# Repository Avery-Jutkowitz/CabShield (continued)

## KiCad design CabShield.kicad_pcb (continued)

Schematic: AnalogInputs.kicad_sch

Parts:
C12, C13, C14, C15: 1uf; C_0603_1608Metric; Manufacturer_Part_Number 0603B105K500XD
D7, D8, D9, D10, D11, D12, D13, D14: 1N4148W-7-F; Nexperia_CFP3_SOD-123W; Manufacturer_Part_Number 1N4148W-7-F
R23, R24, R25, R26, R27, R28, R29, R30: 1k; R_0402_1005Metric_Pad0.72x0.64mm_HandSolder; Manufacturer_Part_Number ERJ-2GEJ102X

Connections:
+3V3: D7.1 (K), D9.1 (K), D11.1 (K), D13.1 (K); also elsewhere on the board
/AI_1: C15.1, D13.2 (A), D14.1 (K), R29.1, R30.2; also elsewhere on the board
/AI_2: C14.1, D11.2 (A), D12.1 (K), R27.1, R28.2; also elsewhere on the board
/AI_3: C13.1, D9.2 (A), D10.1 (K), R25.1, R26.2; also elsewhere on the board
/AI_4: C12.1, D7.2 (A), D8.1 (K), R23.1, R24.2; also elsewhere on the board
/Analog Inputs/AI_conn1: R29.2; also elsewhere on the board
/Analog Inputs/AI_conn2: R27.2; also elsewhere on the board
/Analog Inputs/AI_conn3: R25.2; also elsewhere on the board
/Analog Inputs/AI_conn4: R23.2; also elsewhere on the board
GND: C12.2, C13.2, C14.2, C15.2, D8.2 (A), D10.2 (A), D12.2 (A), D14.2 (A), R24.1, R26.1, R28.1, R30.1; also elsewhere on the board

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
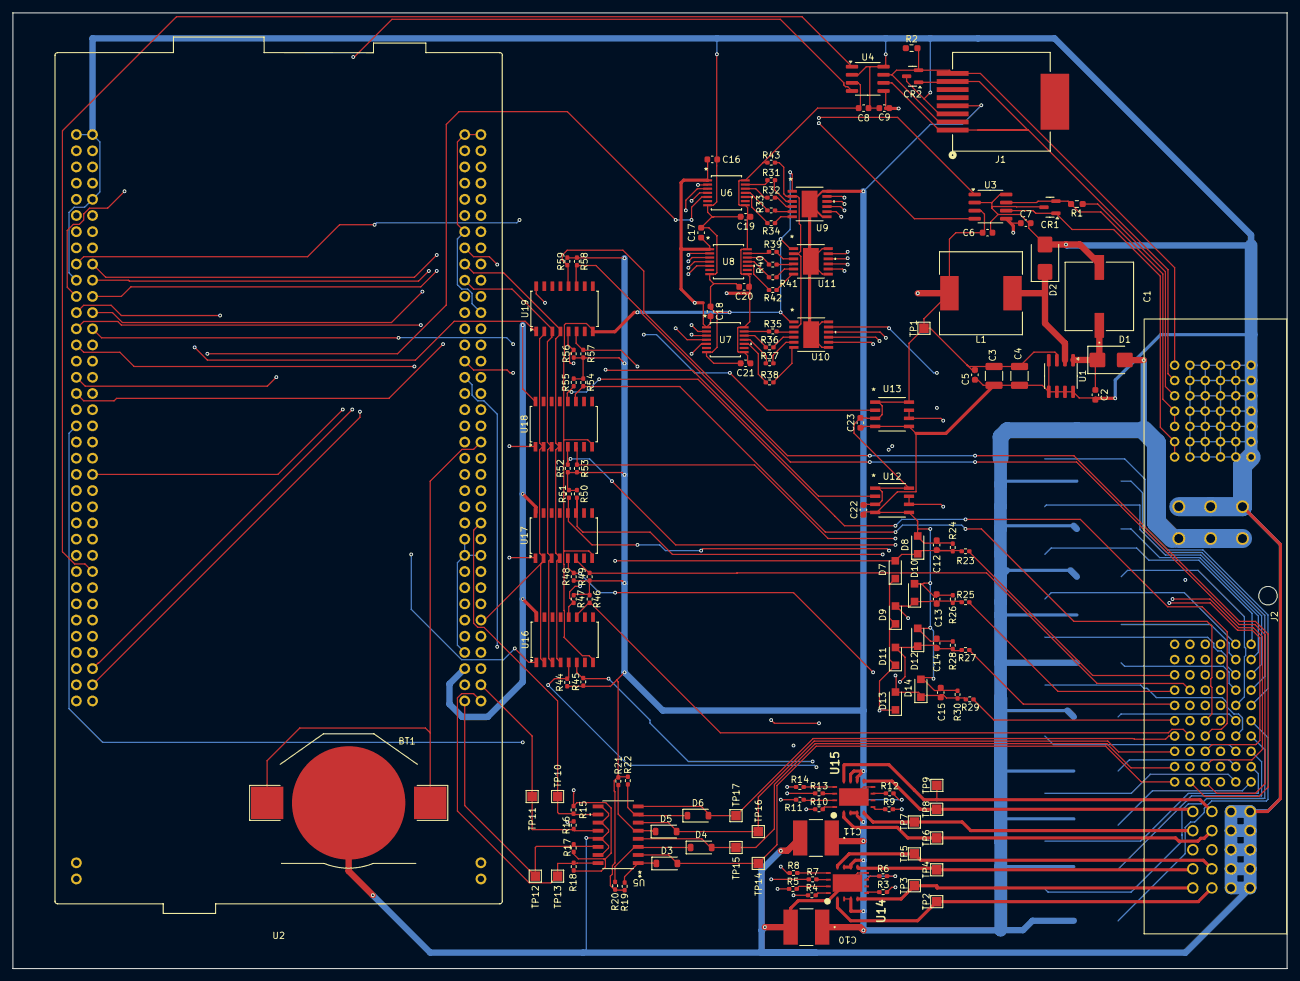
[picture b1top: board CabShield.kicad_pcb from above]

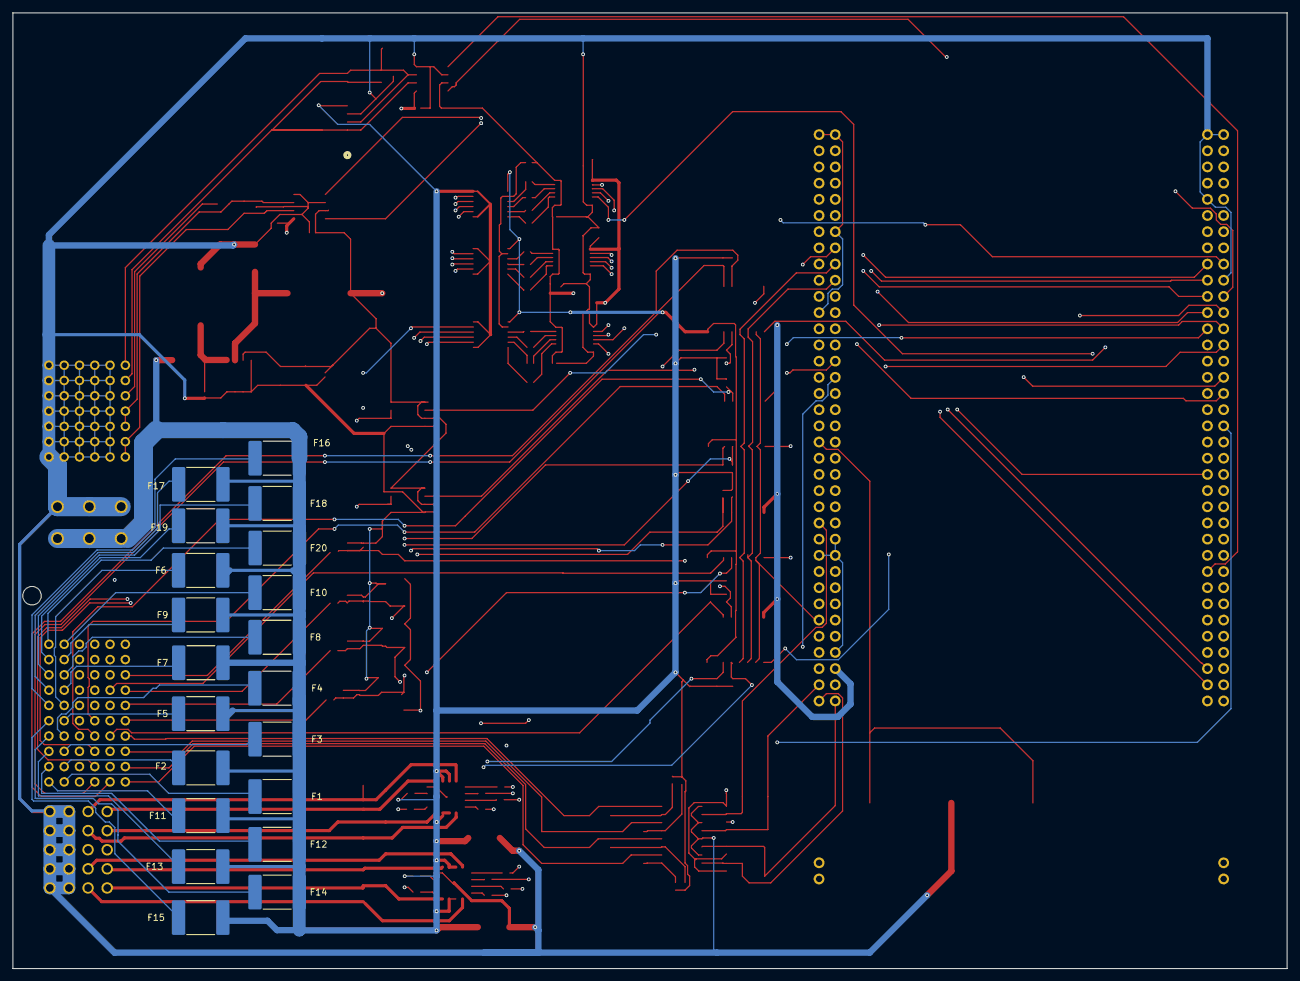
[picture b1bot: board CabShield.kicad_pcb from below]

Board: 4 copper layers, 200.0 x 150.0 mm, 158 parts (20 on the bottom side), 160 nets.

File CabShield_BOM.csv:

"Reference","Value","Description","Manufacturer_Part_Number","Datasheet","Footprint","Qty","DNP"
"BT1","3002","Single-cell battery","3002","https://www.keyelco.com/userAssets/file/M65p9.pdf","Battery:BatteryHolder_Keystone_3002_1x2032","1",""
"C1","EEE-FK1V471SP","Cap 470uF","EEE-FK1V471SP","https://api.pim.na.industrial.panasonic.com/file_stream/main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","HyprLib:CAP_FKS_G_PAN","1",""
"C2,C6,C7,C8,C9,C16,C17,C18,C19,C20,C21,C24,C25","0.1uf","Unpolarized capacitor (0603B104K500XD)","0603B104K500XD","https://mm.digikey.com/Volume0/opasdata/d220001/medias/docus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","Capacitor_SMD:C_0603_1608Metric","13",""
"C3,C4","100uf 6.3V","Polarized capacitor (TAJB107K006RNJ)","TAJB107K006RNJ","https://datasheets.kyocera-avx.com/TAJ.pdf","Capacitor_SMD:C_1210_3225Metric","2",""
"C5,C12,C13,C14,C15,C22,C23","1uf","Unpolarized capacitor (0603B105K500XD)","0603B105K500XD","https://mm.digikey.com/Volume0/opasdata/d220001/medias/docus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","Capacitor_SMD:C_0603_1608Metric","7",""
"C10,C11","100uF","Cap 100uF","CKG57NX7R1V107M500JH","https://product.tdk.com/en/system/files/dam/doc/product/capa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","CAP_CKG57N_TDK","2",""
"CR1,CR2,CR3","PESD1CAN_215","","PESD1CAN_215","https://assets.nexperia.com/documents/data-sheet/PESD1CAN.pdf","Package_TO_SOT_SMD:SOT-23","3",""
"D1,D2","SS45B","40V 2A Schottky Barrier Rectifier Diode, SMB","SS45B","http://www.jameco.com/Jameco/Products/ProdDS/1538777.pdf","Diode_SMD:D_SMB","2",""
"F1,F2,F3,F4,F5,F6,F7,F8,F9,F10,F11,F12,F13,F14,F15,F16,F17,F18,F19,F20","MF-MSMF030","Fuse","MF-MSMF030","https://www.bourns.com/docs/product-datasheets/mf-msmf.pdf?s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","Fuse:Fuse_2920_7451Metric_Pad2.10x5.45mm_HandSolder","20",""
"J1","855135013","RJ45 vertical ","855135013","https://www.molex.com/en-us/products/part-detail/855135013?d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","HyprLib:CONN_85513-5013_MOL","1",""
"J2","~","","","","HyprLib:Compactus128","1","DNP"
"L1","SWRB1207S-680MT","Inductor","SWRB1207S-680MT","https://www.lcsc.com/datasheet/lcsc_datasheet_2310251551_Sun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","Inductor_SMD:L_Sunlord_SWRB1204S","1",""
"R1,R2,R60","120","Resistor (ERJ-3EKF1200V)","ERJ-3EKF1200V","https://industrial.panasonic.com/cdbs/www-data/pdf/RDA0000/A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","Resistor_SMD:R_0603_1608Metric_Pad0.98x0.95mm_HandSolder","3",""
"R3,R9","15K","Resistor (ERJ-2GEJ153X)","ERJ-2GEJ153X","https://api.pim.na.industrial.panasonic.com/file_stream/main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","Resistor_SMD:R_0402_1005Metric_Pad0.72x0.64mm_HandSolder","2",""
"R4,R5,R7,R8,R10,R11,R13,R14,R31,R32,R33,R34,R35,R36,R37,R38,R39,R40,R41,R42,R43","10k","Resistor (ERJ-2GEJ103X)","ERJ-2GEJ103X","https://api.pim.na.industrial.panasonic.com/file_stream/main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","Resistor_SMD:R_0402_1005Metric_Pad0.72x0.64mm_HandSolder","21",""
"R6,R12","20K","Resistor (ERJ-2GEJ203X)","ERJ-2GEJ203X","https://api.pim.na.industrial.panasonic.com/file_stream/main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","Resistor_SMD:R_0402_1005Metric_Pad0.72x0.64mm_HandSolder","2",""
"R15,R16,R17,R18,R19,R20,R21,R22,R23,R24,R25,R26,R27,R28,R29,R30","1k","Resistor (ERJ-2GEJ102X)","ERJ-2GEJ102X","https://api.pim.na.industrial.panasonic.com/file_stream/main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","Resistor_SMD:R_0402_1005Metric_Pad0.72x0.64mm_HandSolder","16",""
"R44,R45,R46,R47,R48,R49,R50,R51,R52,R53,R54,R55,R56,R57,R58,R59","4.7k","Resistor (ERJ-2GEJ472X)","ERJ-2GEJ472X","https://api.pim.na.industrial.panasonic.com/file_stream/main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","Resistor_SMD:R_0402_1005Metric_Pad0.72x0.64mm_HandSolder","16",""
"U1","XL1509-5.0","Buck DC/DC Converter, 2A, 5V Output Voltage, 7-40V Input Voltage","XL1509-5.0","https://datasheet.lcsc.com/lcsc/1809050422_XLSEMI-XL1509-5-0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","Package_SO:SOIC-8_3.9x4.9mm_P1.27mm","1",""
"U2","NUCLEO144-H743ZI","Nucleo 144 Development Board with STM32H743ZIT6 MCU, 1024kB RAM, 2Mb FLASH","","https://www.st.com/resource/en/user_manual/dm00244518-stm32-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","Module:ST_Morpho_Connector_144_STLink","1","DNP"
"U3,U4,U20","MCP2562-E-SN","High-Speed CAN Transceiver, 1Mbps, 5V supply, Vio pin, -40C to +125C, SOIC-8","MCP2562-E-SN","http://ww1.microchip.com/downloads/en/DeviceDoc/25167A.pdf","Package_SO:SOIC-8_3.9x4.9mm_P1.27mm","3",""
"U5","TCMT4100","","TCMT4100","https://www.vishay.com/docs/84181/tcmt4100.pdf","HyprLib:SOP-16_TCMT_VIS","1",""
"U6,U7,U8","TXU0104PWR","","TXU0104PWR","https://www.ti.com/lit/ds/symlink/txu0104.pdf?HQS=dis-dk-nul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","HyprLib:TSSOP_0104PWR_TEX","3",""
"U9,U10,U11","VNQ500PEPTR-E","","VNQ500PEPTR-E","https://www.st.com/content/ccc/resource/technical/document/d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","POWERSSO-12_STM","3",""
"U12,U13","FAN3122TMX","","FAN3122TMX","https://rocelec.widen.net/view/pdf/f6f3uqrtq7/ONSM-S-A000353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","HyprLib:SOIC8_4X5_ONS","2",""
"U14,U15","NIS3071MT3TWG","Electronic fuse (eFuse) 4-channel, 8V to 60V, 10A in 5x6mm package","NIS3071MT3TWG","https://www.onsemi.com/download/data-sheet/pdf/nis3071-d.pdf","HyprLib:QFN105P500X600X80-17N","2",""
"U16,U17,U18,U19","LS7466-S","Tach reader (LS7466-S)","LS7466-S","https://lsicsi.com/wp-content/uploads/2024/04/LS7466.pdf","Package_SO:SOIC-16W_5.3x10.2mm_P1.27mm","4",""
"D3,D4,D5,D6","MMSZ5222BT1G","Diode","MMSZ5222BT1G","https://www.onsemi.com/pdf/datasheet/mmsz5221bt1-d.pdf","Diode_SMD:D_SOD-123","4",""
"D7,D8,D9,D10,D11,D12,D13,D14","1N4148W-7-F","Diode","1N4148W-7-F","https://www.diodes.com/assets/Datasheets/BAV16W_1N4148W.pdf","Diode_SMD:Nexperia_CFP3_SOD-123W","8",""

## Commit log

2024-08-15 added 3rd CAN transiever
2025-03-26 updates to hand built design
2025-03-31 changed Connector Pinout for Nucleo
2025-04-22 new TDU V2 page
